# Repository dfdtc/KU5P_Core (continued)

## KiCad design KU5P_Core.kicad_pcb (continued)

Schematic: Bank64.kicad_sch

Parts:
C258: 100n; C_0201_0603Metric
C259: 10u; C_0603_1608Metric
R47: 240; R_0201_0603Metric
U1: XCKU5P-FFVB676; Xilinx_FFG676
Y1: OB2EL89CEIC112YLC-200M; Oscillator_SMD_SiTime_PQFD-6L_3.2x2.5mm

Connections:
+3V3: C258.1, C259.1, Y1.1 (OE), Y1.6 (VDD); also elsewhere on the board
/FPGA/IO/HP_BANK/Bank64/D4_SYS_CLK_N: U1.AD19 (IO_L14N_T2L_N3_GC_64_N), Y1.5 (OUT-)
/FPGA/IO/HP_BANK/Bank64/D4_SYS_CLK_P: U1.AC19 (IO_L14P_T2L_N2_GC_64_P), Y1.4 (OUT+)
D4.BA0: U1.AC23 (IO_L9N_T1L_N5_AD12N_64_N); also elsewhere on the board
D4.BA1: U1.AA22 (IO_L10P_T1U_N6_QBC_AD4P_64_P); also elsewhere on the board
D4.BG0: U1.AB22 (IO_L10N_T1U_N7_QBC_AD4N_64_N); also elsewhere on the board
D4.CKE: U1.AF20 (IO_T1U_N12_64); also elsewhere on the board
D4.CK_c: U1.AE20 (IO_L13N_T2L_N1_GC_QBC_64_N); also elsewhere on the board
D4.CK_t: U1.AD20 (IO_L13P_T2L_N0_GC_QBC_64_P); also elsewhere on the board
D4.ODT: U1.AB21 (IO_L12P_T1U_N10_GC_64_P); also elsewhere on the board
D4.~ACT: U1.AD21 (IO_L11P_T1U_N8_GC_64_P); also elsewhere on the board
D4.~CS: U1.AE21 (IO_L11N_T1U_N9_GC_64_N); also elsewhere on the board
D4.~RST: U1.AC21 (IO_L12N_T1U_N11_GC_64_N); also elsewhere on the board
D4_ADDR0: U1.AE25 (IO_L1P_T0L_N0_DBC_64_P); also elsewhere on the board
D4_ADDR1: U1.AE26 (IO_L1N_T0L_N1_DBC_64_N); also elsewhere on the board
D4_ADDR2: U1.AB25 (IO_L2P_T0L_N2_64_P); also elsewhere on the board
D4_ADDR3: U1.AB26 (IO_L2N_T0L_N3_64_N); also elsewhere on the board
D4_ADDR4: U1.AF24 (IO_L3P_T0L_N4_AD15P_64_P); also elsewhere on the board
D4_ADDR5: U1.AF25 (IO_L3N_T0L_N5_AD15N_64_N); also elsewhere on the board
D4_ADDR6: U1.AC26 (IO_L4P_T0U_N6_DBC_AD7P_64_P); also elsewhere on the board
D4_ADDR7: U1.AD26 (IO_L4N_T0U_N7_DBC_AD7N_64_N); also elsewhere on the board
D4_ADDR8: U1.AD24 (IO_L5P_T0U_N8_AD14P_64_P); also elsewhere on the board
D4_ADDR9: U1.AD25 (IO_L5N_T0U_N9_AD14N_64_N); also elsewhere on the board
D4_ADDR10: U1.AB24 (IO_L6P_T0U_N10_AD6P_64_P); also elsewhere on the board
D4_ADDR11: U1.AC24 (IO_L6N_T0U_N11_AD6N_64_N); also elsewhere on the board
D4_ADDR12: U1.AE22 (IO_L7P_T1L_N0_QBC_AD13P_64_P); also elsewhere on the board
D4_ADDR13: U1.AF22 (IO_L7N_T1L_N1_QBC_AD13N_64_N); also elsewhere on the board
D4_ADDR14: U1.AD23 (IO_L8P_T1L_N2_AD5P_64_P); also elsewhere on the board
D4_ADDR15: U1.AE23 (IO_L8N_T1L_N3_AD5N_64_N); also elsewhere on the board
D4_ADDR16: U1.AC22 (IO_L9P_T1L_N4_AD12P_64_P); also elsewhere on the board
GND: C258.2, C259.2, R47.2, Y1.3 (GND); also elsewhere on the board
GTY_0_N: U1.AF19 (IO_L15N_T2L_N5_AD11N_64_N); also elsewhere on the board
GTY_0_P: U1.AF18 (IO_L15P_T2L_N4_AD11P_64_P); also elsewhere on the board
GTY_1_N: U1.AD18 (IO_L16N_T2U_N7_QBC_AD3N_64_N); also elsewhere on the board
GTY_1_P: U1.AC18 (IO_L16P_T2U_N6_QBC_AD3P_64_P); also elsewhere on the board
GTY_2_N: U1.AF17 (IO_L17N_T2U_N9_AD10N_64_N); also elsewhere on the board
GTY_2_P: U1.AE17 (IO_L17P_T2U_N8_AD10P_64_P); also elsewhere on the board
GTY_3_N: U1.AE16 (IO_L18N_T2U_N11_AD2N_64_N); also elsewhere on the board
GTY_3_P: U1.AD16 (IO_L18P_T2U_N10_AD2P_64_P); also elsewhere on the board
IO_L19N_T3L_N1_DBC_AD9N_64_N: U1.Y21 (IO_L19N_T3L_N1_DBC_AD9N_64_N)
IO_L19P_T3L_N0_DBC_AD9P_64_P: U1.Y20 (IO_L19P_T3L_N0_DBC_AD9P_64_P)
IO_L20N_T3L_N3_AD1N_64_N: U1.AB19 (IO_L20N_T3L_N3_AD1N_64_N)
IO_L20P_T3L_N2_AD1P_64_P: U1.AA19 (IO_L20P_T3L_N2_AD1P_64_P)
IO_L21N_T3L_N5_AD8N_64_N: U1.AB20 (IO_L21N_T3L_N5_AD8N_64_N)
IO_L21P_T3L_N4_AD8P_64_P: U1.AA20 (IO_L21P_T3L_N4_AD8P_64_P)
IO_L22N_T3U_N7_DBC_AD0N_64_N: U1.AC17 (IO_L22N_T3U_N7_DBC_AD0N_64_N)
IO_L22P_T3U_N6_DBC_AD0P_64_P: U1.AB17 (IO_L22P_T3U_N6_DBC_AD0P_64_P)
IO_L23N_T3U_N9_64_N: U1.AA17 (IO_L23N_T3U_N9_64_N)
IO_L23P_T3U_N8_64_P: U1.Y17 (IO_L23P_T3U_N8_64_P)
IO_L24N_T3U_N11_64_N: U1.AA18 (IO_L24N_T3U_N11_64_N)
IO_L24P_T3U_N10_64_P: U1.Y18 (IO_L24P_T3U_N10_64_P)
IO_T3U_N12_64: U1.AC16 (IO_T3U_N12_64)
unnamed: R47.1, U1.AF23 (IO_T0U_N12_VRP_64)

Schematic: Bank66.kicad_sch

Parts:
R54: 240; R_0201_0603Metric
U1: XCKU5P-FFVB676; Xilinx_FFG676

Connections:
/FPGA/IO/HP_BANK/Bank66/VRP: R54.1, U1.M22 (IO_T0U_N12_VRP_66)
GND: R54.2; also elsewhere on the board
IO_L1N_T0L_N1_DBC_66_N: U1.K18 (IO_L1N_T0L_N1_DBC_66_N); also elsewhere on the board
IO_L1P_T0L_N0_DBC_66_P: U1.L18 (IO_L1P_T0L_N0_DBC_66_P); also elsewhere on the board
IO_L2N_T0L_N3_66_N: U1.M21 (IO_L2N_T0L_N3_66_N); also elsewhere on the board
IO_L2P_T0L_N2_66_P: U1.M20 (IO_L2P_T0L_N2_66_P); also elsewhere on the board
IO_L3N_T0L_N5_AD15N_66_N: U1.J20 (IO_L3N_T0L_N5_AD15N_66_N); also elsewhere on the board
IO_L3P_T0L_N4_AD15P_66_P: U1.J19 (IO_L3P_T0L_N4_AD15P_66_P); also elsewhere on the board
IO_L4N_T0U_N7_DBC_AD7N_66_N: U1.L19 (IO_L4N_T0U_N7_DBC_AD7N_66_N); also elsewhere on the board
IO_L4P_T0U_N6_DBC_AD7P_66_P: U1.M19 (IO_L4P_T0U_N6_DBC_AD7P_66_P); also elsewhere on the board
IO_L5N_T0U_N9_AD14N_66_N: U1.J21 (IO_L5N_T0U_N9_AD14N_66_N); also elsewhere on the board
IO_L5P_T0U_N8_AD14P_66_P: U1.K21 (IO_L5P_T0U_N8_AD14P_66_P); also elsewhere on the board
IO_L6N_T0U_N11_AD6N_66_N: U1.K20 (IO_L6N_T0U_N11_AD6N_66_N); also elsewhere on the board
IO_L6P_T0U_N10_AD6P_66_P: U1.L20 (IO_L6P_T0U_N10_AD6P_66_P); also elsewhere on the board
IO_L7N_T1L_N1_QBC_AD13N_66_N: U1.L23 (IO_L7N_T1L_N1_QBC_AD13N_66_N); also elsewhere on the board
IO_L7P_T1L_N0_QBC_AD13P_66_P: U1.L22 (IO_L7P_T1L_N0_QBC_AD13P_66_P); also elsewhere on the board
IO_L8N_T1L_N3_AD5N_66_N: U1.M26 (IO_L8N_T1L_N3_AD5N_66_N); also elsewhere on the board
IO_L8P_T1L_N2_AD5P_66_P: U1.M25 (IO_L8P_T1L_N2_AD5P_66_P); also elsewhere on the board
IO_L9N_T1L_N5_AD12N_66_N: U1.K26 (IO_L9N_T1L_N5_AD12N_66_N); also elsewhere on the board
IO_L9P_T1L_N4_AD12P_66_P: U1.K25 (IO_L9P_T1L_N4_AD12P_66_P); also elsewhere on the board
IO_L10N_T1U_N7_QBC_AD4N_66_N: U1.L25 (IO_L10N_T1U_N7_QBC_AD4N_66_N); also elsewhere on the board
IO_L10P_T1U_N6_QBC_AD4P_66_P: U1.L24 (IO_L10P_T1U_N6_QBC_AD4P_66_P); also elsewhere on the board
IO_L11N_T1U_N9_GC_66_N: U1.K23 (IO_L11N_T1U_N9_GC_66_N); also elsewhere on the board
IO_L11P_T1U_N8_GC_66_P: U1.K22 (IO_L11P_T1U_N8_GC_66_P); also elsewhere on the board
IO_L12N_T1U_N11_GC_66_N: U1.J24 (IO_L12N_T1U_N11_GC_66_N); also elsewhere on the board
IO_L12P_T1U_N10_GC_66_P: U1.J23 (IO_L12P_T1U_N10_GC_66_P); also elsewhere on the board
IO_L13N_T2L_N1_GC_QBC_66_N: U1.G25 (IO_L13N_T2L_N1_GC_QBC_66_N); also elsewhere on the board
IO_L13P_T2L_N0_GC_QBC_66_P: U1.G24 (IO_L13P_T2L_N0_GC_QBC_66_P); also elsewhere on the board
IO_L14N_T2L_N3_GC_66_N: U1.H24 (IO_L14N_T2L_N3_GC_66_N); also elsewhere on the board
IO_L14P_T2L_N2_GC_66_P: U1.H23 (IO_L14P_T2L_N2_GC_66_P); also elsewhere on the board
IO_L15N_T2L_N5_AD11N_66_N: U1.J26 (IO_L15N_T2L_N5_AD11N_66_N); also elsewhere on the board
IO_L15P_T2L_N4_AD11P_66_P: U1.J25 (IO_L15P_T2L_N4_AD11P_66_P); also elsewhere on the board
IO_L16N_T2U_N7_QBC_AD3N_66_N: U1.F25 (IO_L16N_T2U_N7_QBC_AD3N_66_N); also elsewhere on the board
IO_L16P_T2U_N6_QBC_AD3P_66_P: U1.F24 (IO_L16P_T2U_N6_QBC_AD3P_66_P); also elsewhere on the board
IO_L17N_T2U_N9_AD10N_66_N: U1.G26 (IO_L17N_T2U_N9_AD10N_66_N); also elsewhere on the board
IO_L17P_T2U_N8_AD10P_66_P: U1.H26 (IO_L17P_T2U_N8_AD10P_66_P); also elsewhere on the board
IO_L18N_T2U_N11_AD2N_66_N: U1.H22 (IO_L18N_T2U_N11_AD2N_66_N); also elsewhere on the board
IO_L18P_T2U_N10_AD2P_66_P: U1.H21 (IO_L18P_T2U_N10_AD2P_66_P); also elsewhere on the board
IO_L19N_T3L_N1_DBC_AD9N_66_N: U1.E26 (IO_L19N_T3L_N1_DBC_AD9N_66_N); also elsewhere on the board
IO_L19P_T3L_N0_DBC_AD9P_66_P: U1.E25 (IO_L19P_T3L_N0_DBC_AD9P_66_P); also elsewhere on the board
IO_L20N_T3L_N3_AD1N_66_N: U1.E23 (IO_L20N_T3L_N3_AD1N_66_N); also elsewhere on the board
IO_L20P_T3L_N2_AD1P_66_P: U1.F23 (IO_L20P_T3L_N2_AD1P_66_P); also elsewhere on the board
IO_L21N_T3L_N5_AD8N_66_N: U1.D25 (IO_L21N_T3L_N5_AD8N_66_N); also elsewhere on the board
IO_L21P_T3L_N4_AD8P_66_P: U1.D24 (IO_L21P_T3L_N4_AD8P_66_P); also elsewhere on the board
IO_L22N_T3U_N7_DBC_AD0N_66_N: U1.C24 (IO_L22N_T3U_N7_DBC_AD0N_66_N); also elsewhere on the board
IO_L22P_T3U_N6_DBC_AD0P_66_P: U1.D23 (IO_L22P_T3U_N6_DBC_AD0P_66_P); also elsewhere on the board
IO_L23N_T3U_N9_66_N: U1.C26 (IO_L23N_T3U_N9_66_N); also elsewhere on the board
IO_L23P_T3U_N8_66_P: U1.D26 (IO_L23P_T3U_N8_66_P); also elsewhere on the board
IO_L24N_T3U_N11_66_N: U1.B26 (IO_L24N_T3U_N11_66_N); also elsewhere on the board
IO_L24P_T3U_N10_66_P: U1.B25 (IO_L24P_T3U_N10_66_P); also elsewhere on the board
IO_T1U_N12_66: U1.M24 (IO_T1U_N12_66); also elsewhere on the board
IO_T2U_N12_66: U1.G22 (IO_T2U_N12_66); also elsewhere on the board
IO_T3U_N12_66: U1.F22 (IO_T3U_N12_66); also elsewhere on the board
VCCO_HP: U1.E24 (VCCO_66), U1.H25 (VCCO_66), U1.J22 (VCCO_66); also elsewhere on the board

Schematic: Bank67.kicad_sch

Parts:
R63: 240; R_0201_0603Metric
U1: XCKU5P-FFVB676; Xilinx_FFG676

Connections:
/FPGA/IO/HP_BANK/Bank67/VRP: R63.1, U1.F17 (IO_T0U_N12_VRP_67)
GND: R63.2; also elsewhere on the board
IO_L1N_T0L_N1_DBC_67_N: U1.F15 (IO_L1N_T0L_N1_DBC_67_N); also elsewhere on the board
IO_L1P_T0L_N0_DBC_67_P: U1.G15 (IO_L1P_T0L_N0_DBC_67_P); also elsewhere on the board
IO_L2N_T0L_N3_67_N: U1.G17 (IO_L2N_T0L_N3_67_N); also elsewhere on the board
IO_L2P_T0L_N2_67_P: U1.H17 (IO_L2P_T0L_N2_67_P); also elsewhere on the board
IO_L3N_T0L_N5_AD15N_67_N: U1.D15 (IO_L3N_T0L_N5_AD15N_67_N); also elsewhere on the board
IO_L3P_T0L_N4_AD15P_67_P: U1.E15 (IO_L3P_T0L_N4_AD15P_67_P); also elsewhere on the board
IO_L4N_T0U_N7_DBC_AD7N_67_N: U1.E17 (IO_L4N_T0U_N7_DBC_AD7N_67_N); also elsewhere on the board
IO_L4P_T0U_N6_DBC_AD7P_67_P: U1.E16 (IO_L4P_T0U_N6_DBC_AD7P_67_P); also elsewhere on the board
IO_L5N_T0U_N9_AD14N_67_N: U1.G16 (IO_L5N_T0U_N9_AD14N_67_N); also elsewhere on the board
IO_L5P_T0U_N8_AD14P_67_P: U1.H16 (IO_L5P_T0U_N8_AD14P_67_P); also elsewhere on the board
IO_L6N_T0U_N11_AD6N_67_N: U1.C16 (IO_L6N_T0U_N11_AD6N_67_N); also elsewhere on the board
IO_L6P_T0U_N10_AD6P_67_P: U1.D16 (IO_L6P_T0U_N10_AD6P_67_P); also elsewhere on the board
IO_L7N_T1L_N1_QBC_AD13N_67_N: U1.H19 (IO_L7N_T1L_N1_QBC_AD13N_67_N); also elsewhere on the board
IO_L7P_T1L_N0_QBC_AD13P_67_P: U1.H18 (IO_L7P_T1L_N0_QBC_AD13P_67_P); also elsewhere on the board
IO_L8N_T1L_N3_AD5N_67_N: U1.F19 (IO_L8N_T1L_N3_AD5N_67_N); also elsewhere on the board
IO_L8P_T1L_N2_AD5P_67_P: U1.F18 (IO_L8P_T1L_N2_AD5P_67_P); also elsewhere on the board
IO_L9N_T1L_N5_AD12N_67_N: U1.G21 (IO_L9N_T1L_N5_AD12N_67_N); also elsewhere on the board
IO_L9P_T1L_N4_AD12P_67_P: U1.G20 (IO_L9P_T1L_N4_AD12P_67_P); also elsewhere on the board
IO_L10N_T1U_N7_QBC_AD4N_67_N: U1.E20 (IO_L10N_T1U_N7_QBC_AD4N_67_N); also elsewhere on the board
IO_L10P_T1U_N6_QBC_AD4P_67_P: U1.F20 (IO_L10P_T1U_N6_QBC_AD4P_67_P); also elsewhere on the board
IO_L11N_T1U_N9_GC_67_N: U1.D18 (IO_L11N_T1U_N9_GC_67_N); also elsewhere on the board
IO_L11P_T1U_N8_GC_67_P: U1.E18 (IO_L11P_T1U_N8_GC_67_P); also elsewhere on the board
IO_L12N_T1U_N11_GC_67_N: U1.D20 (IO_L12N_T1U_N11_GC_67_N); also elsewhere on the board
IO_L12P_T1U_N10_GC_67_P: U1.D19 (IO_L12P_T1U_N10_GC_67_P); also elsewhere on the board
IO_L13N_T2L_N1_GC_QBC_67_N: U1.C19 (IO_L13N_T2L_N1_GC_QBC_67_N); also elsewhere on the board
IO_L13P_T2L_N0_GC_QBC_67_P: U1.C18 (IO_L13P_T2L_N0_GC_QBC_67_P); also elsewhere on the board
IO_L14N_T2L_N3_GC_67_N: U1.B20 (IO_L14N_T2L_N3_GC_67_N); also elsewhere on the board
IO_L14P_T2L_N2_GC_67_P: U1.B19 (IO_L14P_T2L_N2_GC_67_P); also elsewhere on the board
IO_L15N_T2L_N5_AD11N_67_N: U1.B17 (IO_L15N_T2L_N5_AD11N_67_N); also elsewhere on the board
IO_L15P_T2L_N4_AD11P_67_P: U1.C17 (IO_L15P_T2L_N4_AD11P_67_P); also elsewhere on the board
IO_L16N_T2U_N7_QBC_AD3N_67_N: U1.A18 (IO_L16N_T2U_N7_QBC_AD3N_67_N); also elsewhere on the board
IO_L16P_T2U_N6_QBC_AD3P_67_P: U1.A17 (IO_L16P_T2U_N6_QBC_AD3P_67_P); also elsewhere on the board
IO_L17N_T2U_N9_AD10N_67_N: U1.A15 (IO_L17N_T2U_N9_AD10N_67_N); also elsewhere on the board
IO_L17P_T2U_N8_AD10P_67_P: U1.B15 (IO_L17P_T2U_N8_AD10P_67_P); also elsewhere on the board
IO_L18N_T2U_N11_AD2N_67_N: U1.A20 (IO_L18N_T2U_N11_AD2N_67_N); also elsewhere on the board
IO_L18P_T2U_N10_AD2P_67_P: U1.A19 (IO_L18P_T2U_N10_AD2P_67_P); also elsewhere on the board
IO_L19N_T3L_N1_DBC_AD9N_67_N: U1.A23 (IO_L19N_T3L_N1_DBC_AD9N_67_N); also elsewhere on the board
IO_L19P_T3L_N0_DBC_AD9P_67_P: U1.A22 (IO_L19P_T3L_N0_DBC_AD9P_67_P); also elsewhere on the board
IO_L20N_T3L_N3_AD1N_67_N: U1.D21 (IO_L20N_T3L_N3_AD1N_67_N); also elsewhere on the board
IO_L20P_T3L_N2_AD1P_67_P: U1.E21 (IO_L20P_T3L_N2_AD1P_67_P); also elsewhere on the board
IO_L21N_T3L_N5_AD8N_67_N: U1.B24 (IO_L21N_T3L_N5_AD8N_67_N); also elsewhere on the board
IO_L21P_T3L_N4_AD8P_67_P: U1.C23 (IO_L21P_T3L_N4_AD8P_67_P); also elsewhere on the board
IO_L22N_T3U_N7_DBC_AD0N_67_N: U1.B21 (IO_L22N_T3U_N7_DBC_AD0N_67_N); also elsewhere on the board
IO_L22P_T3U_N6_DBC_AD0P_67_P: U1.C21 (IO_L22P_T3U_N6_DBC_AD0P_67_P); also elsewhere on the board
IO_L23N_T3U_N9_67_N: U1.A25 (IO_L23N_T3U_N9_67_N); also elsewhere on the board
IO_L23P_T3U_N8_67_P: U1.A24 (IO_L23P_T3U_N8_67_P); also elsewhere on the board
IO_L24N_T3U_N11_67_N: U1.B22 (IO_L24N_T3U_N11_67_N); also elsewhere on the board
IO_L24P_T3U_N10_67_P: U1.C22 (IO_L24P_T3U_N10_67_P); also elsewhere on the board
IO_T1U_N12_67: U1.G19 (IO_T1U_N12_67); also elsewhere on the board
IO_T2U_N12_67: U1.B16 (IO_T2U_N12_67); also elsewhere on the board
IO_T3U_N12_67: U1.E22 (IO_T3U_N12_67); also elsewhere on the board
VCCO_HP: U1.C20 (VCCO_67), U1.D17 (VCCO_67), U1.G18 (VCCO_67); also elsewhere on the board

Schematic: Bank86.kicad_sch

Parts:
U1: XCKU5P-FFVB676; Xilinx_FFG676

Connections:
IO_L1N_AD11N_86_N: U1.K9 (IO_L1N_AD11N_86_N); also elsewhere on the board
IO_L1P_AD11P_86_P: U1.K10 (IO_L1P_AD11P_86_P); also elsewhere on the board
IO_L2N_AD10N_86_N: U1.J10 (IO_L2N_AD10N_86_N); also elsewhere on the board
IO_L2P_AD10P_86_P: U1.J11 (IO_L2P_AD10P_86_P); also elsewhere on the board
IO_L3N_AD9N_86_N: U1.H9 (IO_L3N_AD9N_86_N); also elsewhere on the board
IO_L3P_AD9P_86_P: U1.J9 (IO_L3P_AD9P_86_P); also elsewhere on the board
IO_L4N_AD8N_86_N: U1.G11 (IO_L4N_AD8N_86_N); also elsewhere on the board
IO_L4P_AD8P_86_P: U1.H11 (IO_L4P_AD8P_86_P); also elsewhere on the board
IO_L5N_HDGC_AD7N_86_N: U1.G9 (IO_L5N_HDGC_AD7N_86_N); also elsewhere on the board
IO_L5P_HDGC_AD7P_86_P: U1.G10 (IO_L5P_HDGC_AD7P_86_P); also elsewhere on the board
IO_L6N_HDGC_AD6N_86_N: U1.F9 (IO_L6N_HDGC_AD6N_86_N); also elsewhere on the board
IO_L6P_HDGC_AD6P_86_P: U1.F10 (IO_L6P_HDGC_AD6P_86_P); also elsewhere on the board
IO_L7N_HDGC_AD5N_86_N: U1.E10 (IO_L7N_HDGC_AD5N_86_N); also elsewhere on the board
IO_L7P_HDGC_AD5P_86_P: U1.E11 (IO_L7P_HDGC_AD5P_86_P); also elsewhere on the board
IO_L8N_HDGC_AD4N_86_N: U1.D10 (IO_L8N_HDGC_AD4N_86_N); also elsewhere on the board
IO_L8P_HDGC_AD4P_86_P: U1.D11 (IO_L8P_HDGC_AD4P_86_P); also elsewhere on the board
IO_L9N_AD3N_86_N: U1.C9 (IO_L9N_AD3N_86_N); also elsewhere on the board
IO_L9P_AD3P_86_P: U1.D9 (IO_L9P_AD3P_86_P); also elsewhere on the board
IO_L10N_AD2N_86_N: U1.A9 (IO_L10N_AD2N_86_N); also elsewhere on the board
IO_L10P_AD2P_86_P: U1.B9 (IO_L10P_AD2P_86_P); also elsewhere on the board
IO_L11N_AD1N_86_N: U1.A10 (IO_L11N_AD1N_86_N); also elsewhere on the board
IO_L11P_AD1P_86_P: U1.B10 (IO_L11P_AD1P_86_P); also elsewhere on the board
IO_L12N_AD0N_86_N: U1.B11 (IO_L12N_AD0N_86_N); also elsewhere on the board
IO_L12P_AD0P_86_P: U1.C11 (IO_L12P_AD0P_86_P); also elsewhere on the board
VCCO_HD: U1.E9 (VCCO_86), U1.H10 (VCCO_86); also elsewhere on the board

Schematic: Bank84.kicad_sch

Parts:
U1: XCKU5P-FFVB676; Xilinx_FFG676

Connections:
IO_L1N_AD11N_84_N: U1.AF15 (IO_L1N_AD11N_84_N); also elsewhere on the board
IO_L1P_AD11P_84_P: U1.AF14 (IO_L1P_AD11P_84_P); also elsewhere on the board
IO_L2N_AD10N_84_N: U1.AF13 (IO_L2N_AD10N_84_N); also elsewhere on the board
IO_L2P_AD10P_84_P: U1.AE13 (IO_L2P_AD10P_84_P); also elsewhere on the board
IO_L3N_AD9N_84_N: U1.AE15 (IO_L3N_AD9N_84_N); also elsewhere on the board
IO_L3P_AD9P_84_P: U1.AD15 (IO_L3P_AD9P_84_P); also elsewhere on the board
IO_L4N_AD8N_84_N: U1.AD14 (IO_L4N_AD8N_84_N); also elsewhere on the board
IO_L4P_AD8P_84_P: U1.AD13 (IO_L4P_AD8P_84_P); also elsewhere on the board
IO_L5N_HDGC_AD7N_84_N: U1.AC14 (IO_L5N_HDGC_AD7N_84_N); also elsewhere on the board
IO_L5P_HDGC_AD7P_84_P: U1.AC13 (IO_L5P_HDGC_AD7P_84_P); also elsewhere on the board
IO_L6N_HDGC_AD6N_84_N: U1.AB16 (IO_L6N_HDGC_AD6N_84_N); also elsewhere on the board
IO_L6P_HDGC_AD6P_84_P: U1.AB15 (IO_L6P_HDGC_AD6P_84_P); also elsewhere on the board
IO_L7N_HDGC_AD5N_84_N: U1.AA15 (IO_L7N_HDGC_AD5N_84_N); also elsewhere on the board
IO_L7P_HDGC_AD5P_84_P: U1.Y15 (IO_L7P_HDGC_AD5P_84_P); also elsewhere on the board
IO_L8N_HDGC_AD4N_84_N: U1.AB14 (IO_L8N_HDGC_AD4N_84_N); also elsewhere on the board
IO_L8P_HDGC_AD4P_84_P: U1.AA14 (IO_L8P_HDGC_AD4P_84_P); also elsewhere on the board
IO_L9N_AD3N_84_N: U1.Y16 (IO_L9N_AD3N_84_N); also elsewhere on the board
IO_L9P_AD3P_84_P: U1.W16 (IO_L9P_AD3P_84_P); also elsewhere on the board
IO_L10N_AD2N_84_N: U1.W15 (IO_L10N_AD2N_84_N); also elsewhere on the board
IO_L10P_AD2P_84_P: U1.W14 (IO_L10P_AD2P_84_P); also elsewhere on the board
IO_L11N_AD1N_84_N: U1.AA13 (IO_L11N_AD1N_84_N); also elsewhere on the board
IO_L11P_AD1P_84_P: U1.Y13 (IO_L11P_AD1P_84_P); also elsewhere on the board
IO_L12N_AD0N_84_N: U1.W13 (IO_L12N_AD0N_84_N); also elsewhere on the board
IO_L12P_AD0P_84_P: U1.W12 (IO_L12P_AD0P_84_P); also elsewhere on the board
VCCO_HD: U1.AC15 (VCCO_84), U1.Y14 (VCCO_84); also elsewhere on the board

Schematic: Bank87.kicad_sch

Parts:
U1: XCKU5P-FFVB676; Xilinx_FFG676

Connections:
ALERT_M: U1.J13 (IO_L2P_AD14P_87_P); also elsewhere on the board
ALERT_S: U1.H13 (IO_L2N_AD14N_87_N); also elsewhere on the board
FAN_PWM: U1.J15 (IO_L4P_AD12P_87_P); also elsewhere on the board
FAN_TACH: U1.F12 (IO_L5N_HDGC_87_N); also elsewhere on the board
GTY_AUX_a: U1.J14 (IO_L4N_AD12N_87_N); also elsewhere on the board
GTY_AUX_b: U1.G12 (IO_L5P_HDGC_87_P); also elsewhere on the board
IO_L6N_HDGC_87_N: U1.F13 (IO_L6N_HDGC_87_N); also elsewhere on the board
IO_L7N_HDGC_87_N: U1.E12 (IO_L7N_HDGC_87_N); also elsewhere on the board
IO_L7P_HDGC_87_P: U1.E13 (IO_L7P_HDGC_87_P); also elsewhere on the board
IO_L8N_HDGC_87_N: U1.D13 (IO_L8N_HDGC_87_N); also elsewhere on the board
IO_L8P_HDGC_87_P: U1.D14 (IO_L8P_HDGC_87_P); also elsewhere on the board
IO_L9N_AD11N_87_N: U1.C13 (IO_L9N_AD11N_87_N); also elsewhere on the board
IO_L9P_AD11P_87_P: U1.C14 (IO_L9P_AD11P_87_P); also elsewhere on the board
IO_L10N_AD10N_87_N: U1.B12 (IO_L10N_AD10N_87_N); also elsewhere on the board
IO_L10P_AD10P_87_P: U1.C12 (IO_L10P_AD10P_87_P); also elsewhere on the board
IO_L11N_AD9N_87_N: U1.A12 (IO_L11N_AD9N_87_N); also elsewhere on the board
IO_L11P_AD9P_87_P: U1.A13 (IO_L11P_AD9P_87_P); also elsewhere on the board
IO_L12N_AD8N_87_N: U1.A14 (IO_L12N_AD8N_87_N); also elsewhere on the board
IO_L12P_AD8P_87_P: U1.B14 (IO_L12P_AD8P_87_P); also elsewhere on the board
P1_GPIO: U1.G14 (IO_L3N_AD13N_87_N); also elsewhere on the board
P1_INT: U1.H14 (IO_L3P_AD13P_87_P); also elsewhere on the board
PMIC_32KOUT: U1.F14 (IO_L6P_HDGC_87_P); also elsewhere on the board
Power_SCL: U1.H12 (IO_L1N_AD15N_87_N); also elsewhere on the board
Power_SDA: U1.J12 (IO_L1P_AD15P_87_P); also elsewhere on the board
VCCO_HD87: U1.E14 (VCCO_87), U1.H15 (VCCO_87); also elsewhere on the board

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
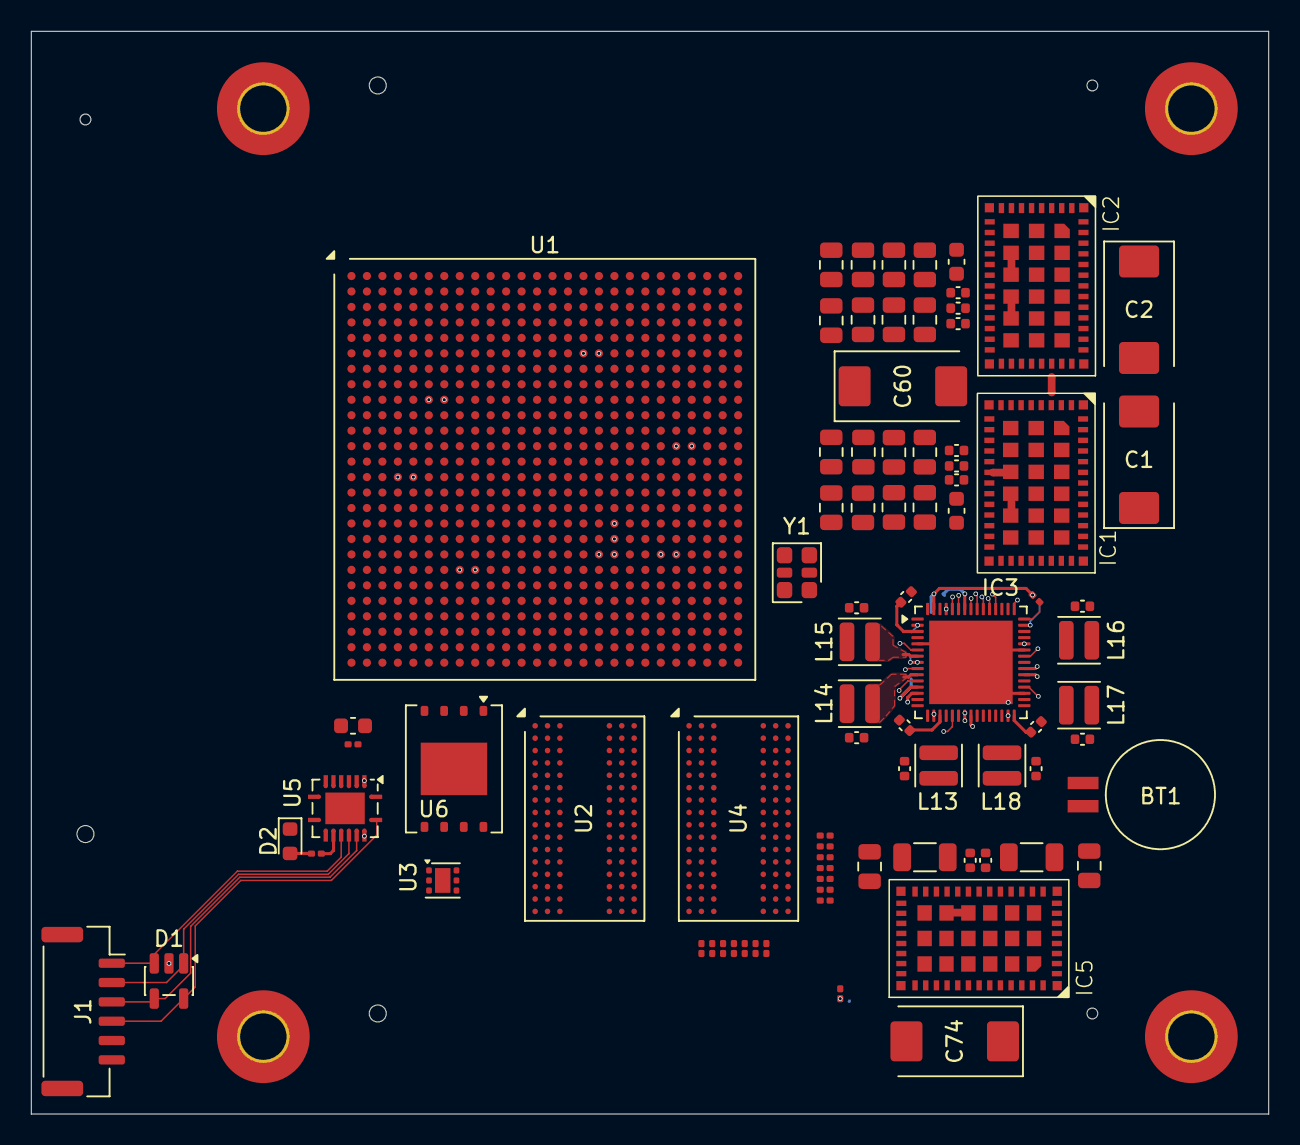
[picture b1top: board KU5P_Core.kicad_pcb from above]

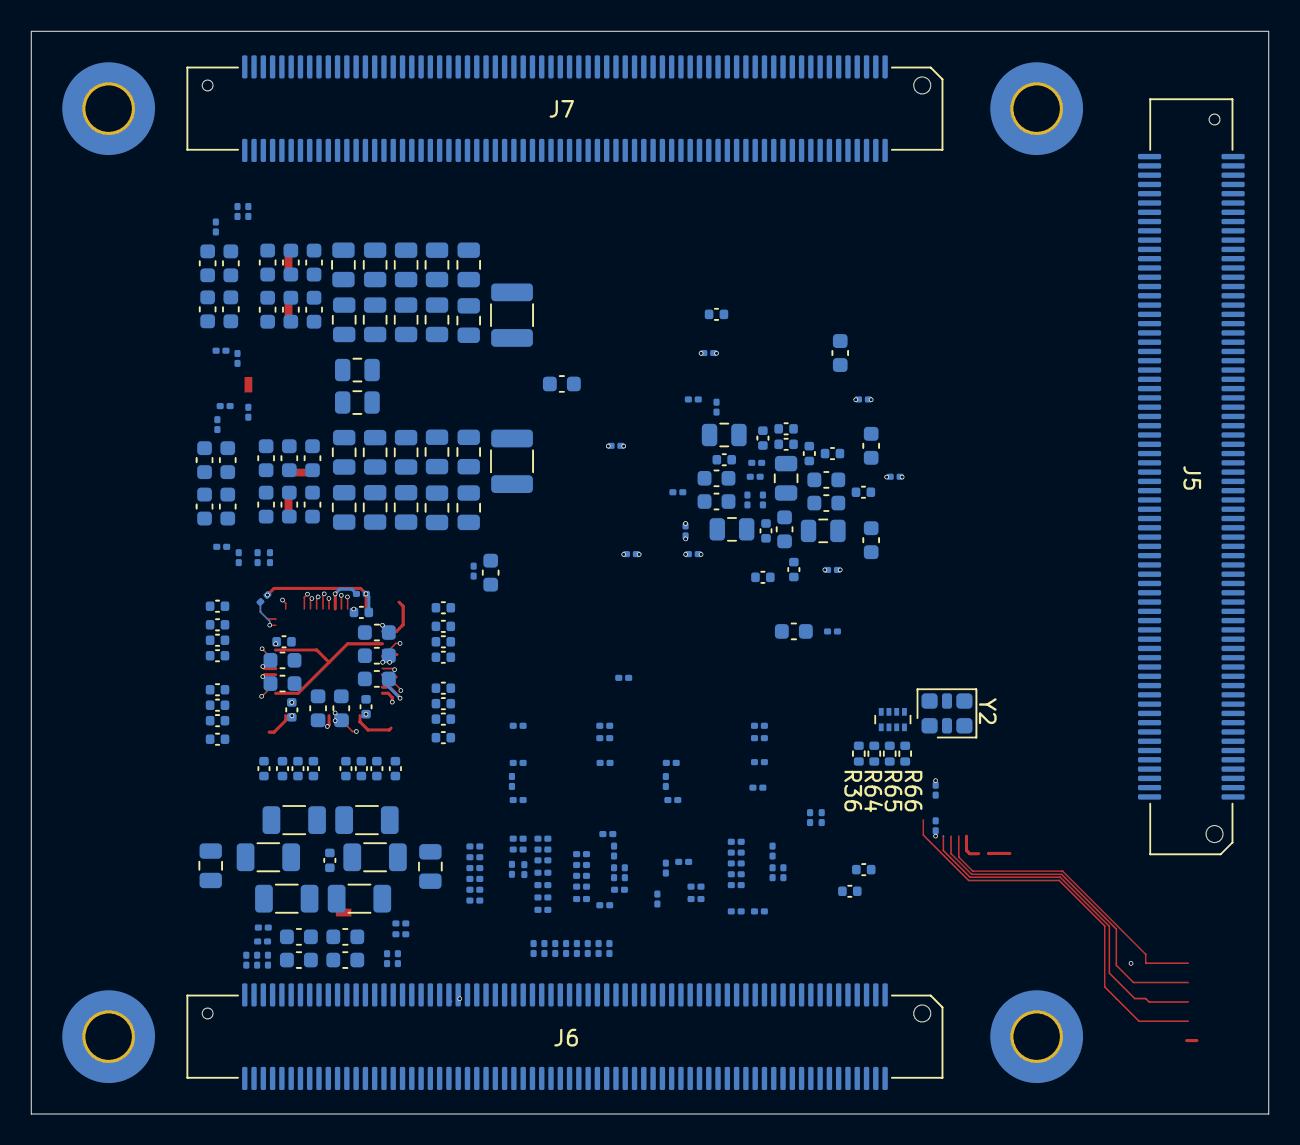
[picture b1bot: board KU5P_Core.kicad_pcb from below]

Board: 8 copper layers, 80.0 x 70.0 mm, 332 parts (239 on the bottom side), 432 nets.
